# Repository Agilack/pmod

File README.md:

# PMOD modules

This repository contains multiple projects of PMOD modules. All of them are
used for communications.

## CAN

This module is a peripheral interface to connect a CAN bus.

## RS232

This module is a RS232 interface. The PMOD side is a type4a interface and
the other side is a DB9 male connector. The module contains a level shifter
(basically a MAX3232) to allow interfacing RS232 signal levels on a board
with TTL levels.

## RS485

## Midi (IN)

This module can be used to connect a MIDI device to a board with PMOD interface.
The MIDI port is an input, so only instruments that send datas can be connected
(tested with a keyboard)

## USB Serial

This module is an usb-serial adapter (PMOD peripheral). Based on a Silicon Labs
chip, no specific driver is required to use it on most OS.

## Wifi

This module is a Wifi interface (PMOD peripheral). Based on the very popular
espressif chip (ESP8285 or ESP8266)

# License

All electronics parts are released under Creative Commons Attribution Share
Alike 3.0 license.

All firmwares and softwares included with modules are realeased under GNU
General Public Licence v3 (GNU GPLv3)

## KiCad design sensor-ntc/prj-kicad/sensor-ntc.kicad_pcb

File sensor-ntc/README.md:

NTC Sensor
==========

This PMOD peripheral is a data acquisition module for temperature sensor (NTC).

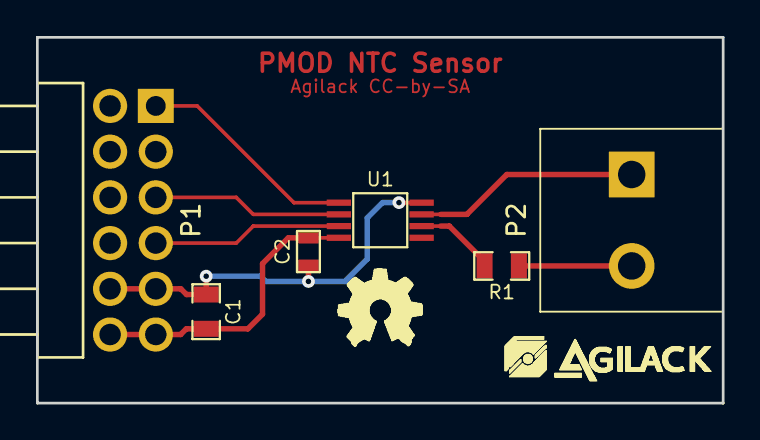
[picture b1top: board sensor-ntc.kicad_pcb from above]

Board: 2 copper layers, 38.1 x 20.3 mm, 8 parts (0 on the bottom side), 8 nets.

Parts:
C1: 1uF; SMD0805
C2: 100nF; SMD0603
P1: PMOD; CONN_PMOD-Male
P2: CONN_2; CONN_MC000034
R1: R; SMD0805
U1: MAX6682; MSOP8
agilack-11.5: 450px; logo-agilack-11.5
ohw_logo: VAL**; Logo-ohw

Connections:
GND: C1.2, C2.2, P1.5, P1.11, U1.4
unnamed: P2.1, U1.3
unnamed: P2.2, R1.2
unnamed: R1.1, U1.2
SPI_CS: P1.1, U1.5
SPI_MISO: P1.3, U1.6
SPI_SCK: P1.4, U1.7
VCC: C1.1, C2.1, P1.6, P1.12, U1.8

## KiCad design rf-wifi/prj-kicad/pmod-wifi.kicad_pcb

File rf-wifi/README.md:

PMOD Wifi
=========

This PMOD peripheral allow to quickly add a Wifi interface to a development
board. The embedded espressif chip (ESP8285 or ESP8266) can act as a station
(client) or as an access point (AP).

The PMOD connector use a type 4A interface (UART 12 pins).

Design
------

            Schematics            |              Routing
--------------------------------- | ---------------------------------
 |

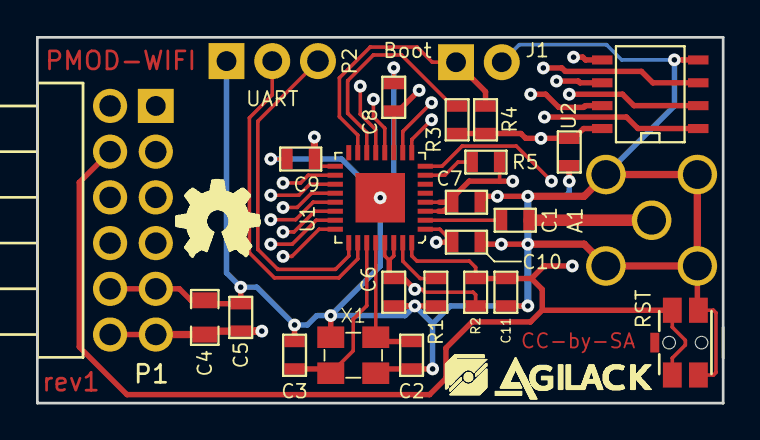
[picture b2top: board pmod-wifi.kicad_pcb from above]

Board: 4 copper layers, 38.1 x 20.3 mm, 27 parts (0 on the bottom side), 24 nets.

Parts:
A1: ANTENNA; CONN_SMA_RA
C1: 5.6pF; SMD0603
C2, C3: 10pF; SMD0603
C4: 10uF; SMD0805
C5, C6, C7, C8, C9, C10, C12: 100nF; SMD0603
C11: 1uF; SMD0603
J1: JUMPER; CONN_2
LOGO-OHW: VAL**; logo-ohw
P1: PMOD; CONN_PMOD-Male
P2: CONN_3
R1: 12k; SMD0603
R2, R3, R4, R5: 10k; SMD0603
SW1: SW_PUSH; SW_PTS840
U1: ESP8285; QFN32
U2: M25P16-VME; SOIC-8E
X1: 26MHz; Q_3.2x2.5
agilack-11.5: 450px; logo-agilack-11.5

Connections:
+3.3V: C4.1, C5.1, C6.1, C7.1, C8.1, C9.1, C10.1, C12.1, P1.6, P1.12, R2.1, R3.1, R4.1, R5.1, U1.1, U1.3, U1.4, U1.11, U1.17, U1.29, U1.30, U2.8
/CFG1: R3.2, U1.14
BOOT: J1.1, R4.2, U1.15
GND: A1.2, C2.2, C3.2, C4.2, C5.2, C6.2, C7.2, C8.2, C9.2, C10.2, C11.2, C12.2, J1.2, P1.5, P1.11, P2.1, R1.2, SW1.2, U1.PAD, U2.4, X1.2, X1.4
MEM_CLK: U1.21, U2.6
MEM_CS: U1.20, U2.1
MEM_HOLD: U1.18, U2.7
MEM_MISO: U1.22, U2.2
MEM_MOSI: U1.23, U2.5
MEM_WP: U1.19, U2.3
unnamed: A1.1, C1.1
unnamed: C1.2, U1.2
unnamed: C2.1, U1.28, X1.3
unnamed: C3.1, U1.27, X1.1
unnamed: R1.1, U1.31
unnamed: R5.2, U1.7
RST: C11.1, P1.8, R2.2, SW1.1, U1.8, U1.32
SPI_CS: P1.1, U1.13
SPI_INT: P1.7, U1.24
SPI_MISO: P1.3, U1.10
SPI_MOSI: P1.2, U1.12
SPI_SCK: P1.4, U1.9
UART_RX: P2.3, U1.25
UART_TX: P2.2, U1.26

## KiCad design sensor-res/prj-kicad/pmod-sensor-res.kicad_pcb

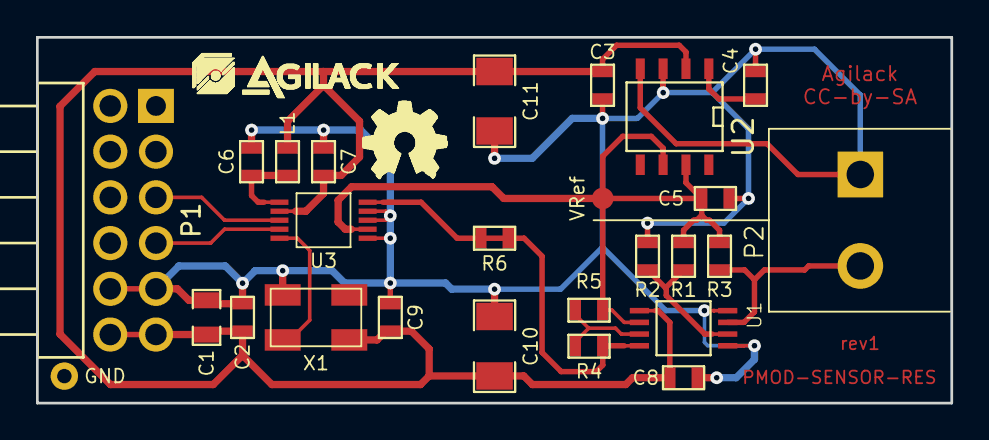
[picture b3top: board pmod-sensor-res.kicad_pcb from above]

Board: 2 copper layers, 50.8 x 20.3 mm, 28 parts (0 on the bottom side), 12 nets.

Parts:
C1: 10uF; SMD0805
C2, C3, C4, C6, C7, C8, C9: 100nF; SMD0603
C5: 1uF; SMD0603
C10, C11: 2,2uF; SMD1206
L1: FB100; SMD0603
LOGO-OHW: VAL**; logo-ohw
P1: PMOD; CONN_PMOD-Male
P2: CONN_2; MC000034
R1, R3: 10k; SMD0603
R2: 100; SMD0603
R4, R5: R; SMD0603
R6: 0; SMD0603
TP1: CONN_1; TP_SMD
TP2: CONN_1; TP
U1: AD8237; TSSOP8
U2: MAX6126; SOIC-8E
U3: MAX11201; MSOP-10
X1: OSC; Q_SMD5x3
agilack-11.5: 450px; logo-agilack-11.5

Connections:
+3.3V: C1.1, C2.1, C3.1, C7.1, C8.1, C9.1, C10.1, C11.1, L1.1, P1.6, P1.12, U1.5, U2.2, U3.7, X1.4
+VSensor: C5.1, R1.2, R3.1, R5.1, TP1.1, U1.6, U2.6, U2.7, U3.2
/S_IN: P2.2, R3.2, U1.3
/S_REF: R1.1, R2.2, U1.2
GND: C1.2, C2.2, C3.2, C4.2, C5.2, C6.2, C7.2, C8.2, C9.2, C10.2, C11.2, P1.5, P1.11, P2.1, R2.1, TP2.1, U1.1, U1.4, U2.3, U2.4, U3.1, U3.3, U3.4, X1.2
MCLK: U3.10, X1.3
unnamed: C4.1, U2.1
unnamed: C6.1, L1.2, U3.6
unnamed: R4.1, R5.2, U1.7
unnamed: R4.2, R6.1, R6.2, U1.8, U3.5
SPI_MISO: P1.3, U3.8
SPI_SCK: P1.4, U3.9

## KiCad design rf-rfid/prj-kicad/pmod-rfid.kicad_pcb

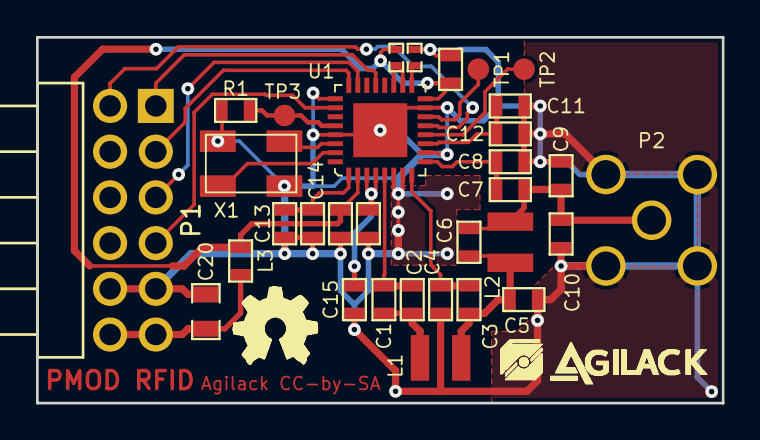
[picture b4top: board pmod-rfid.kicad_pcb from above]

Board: 2 copper layers, 38.1 x 20.3 mm, 34 parts (0 on the bottom side), 24 nets.

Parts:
C1, C2: 1,5nF; SMD0603
C3, C4: 1,2nF; SMD0603
C5, C8: 680pF; SMD0603
C6: 10pF; SMD0603
C7: 220pF; SMD0603
C9: 100pF; SMD0603
C10: 27pF; SMD0603
C11, C13, C15: 2,2uF; SMD0603
C12, C14, C16: 10nF; SMD0603
C18, C19: 100nF; SMD0603
C20: C; SMD0805
L1: INDUCTOR; I_1008CS
L2: 330nH; I_1008CS
L3: FB1000; SMD0603
P1: PMOD; CONN_PMOD-Male
P2: ANTENNA; CONN_SMA_RA
R1: 10k; SMD0603
R2, R3: 0; SMD0402
TP1, TP2, TP3: CONN_1; TP_SMD
U1: TRF7970; QFN32
X1: 13,56MHz; Q_SMD5x3
agilack-11.5: 450px; logo-agilack-11.5
ohw_logo: VAL**; logo-ohw

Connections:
+3.3V: C20.1, L3.1, P1.6, P1.12
+Vrfid: C18.1, C19.1, L3.2, R3.1, U1.2, U1.16
GND: C4.2, C5.2, C8.2, C9.2, C10.2, C11.2, C12.2, C13.2, C14.2, C15.2, C16.2, C18.2, C19.2, C20.2, P1.5, P1.11, P2.2, R1.1, R2.2, U1.6, U1.7, U1.10, U1.15, U1.25, U1.29, U1.PAD, X1.2, X1.4
unnamed: C1.1, C2.1, L1.1
unnamed: C1.2, C2.2, U1.5
unnamed: C3.1, C5.1, C6.2, L1.2, L2.1
unnamed: C3.2, C4.1, U1.8
unnamed: C7.2, C8.1, U1.9
unnamed: C6.1, C7.1, C9.1, C10.1, L2.2, P2.1
unnamed: C11.1, C12.1, U1.11
unnamed: C13.1, C14.1, U1.1
unnamed: C15.1, C16.1, U1.3, U1.4
unnamed: R1.2, TP3.1, U1.28
unnamed: TP1.1, U1.14
unnamed: TP2.1, U1.12
unnamed: U1.30, X1.3
unnamed: U1.31, X1.1
SPI_CFG0: R2.1, U1.17
SPI_CFG1: R3.2, U1.18, U1.19
SPI_IT: P1.7, U1.13
SPI_MISO: P1.3, U1.23
SPI_MOSI: P1.2, U1.24
SPI_NSS: P1.1, U1.21
SPI_SCK: P1.4, U1.26

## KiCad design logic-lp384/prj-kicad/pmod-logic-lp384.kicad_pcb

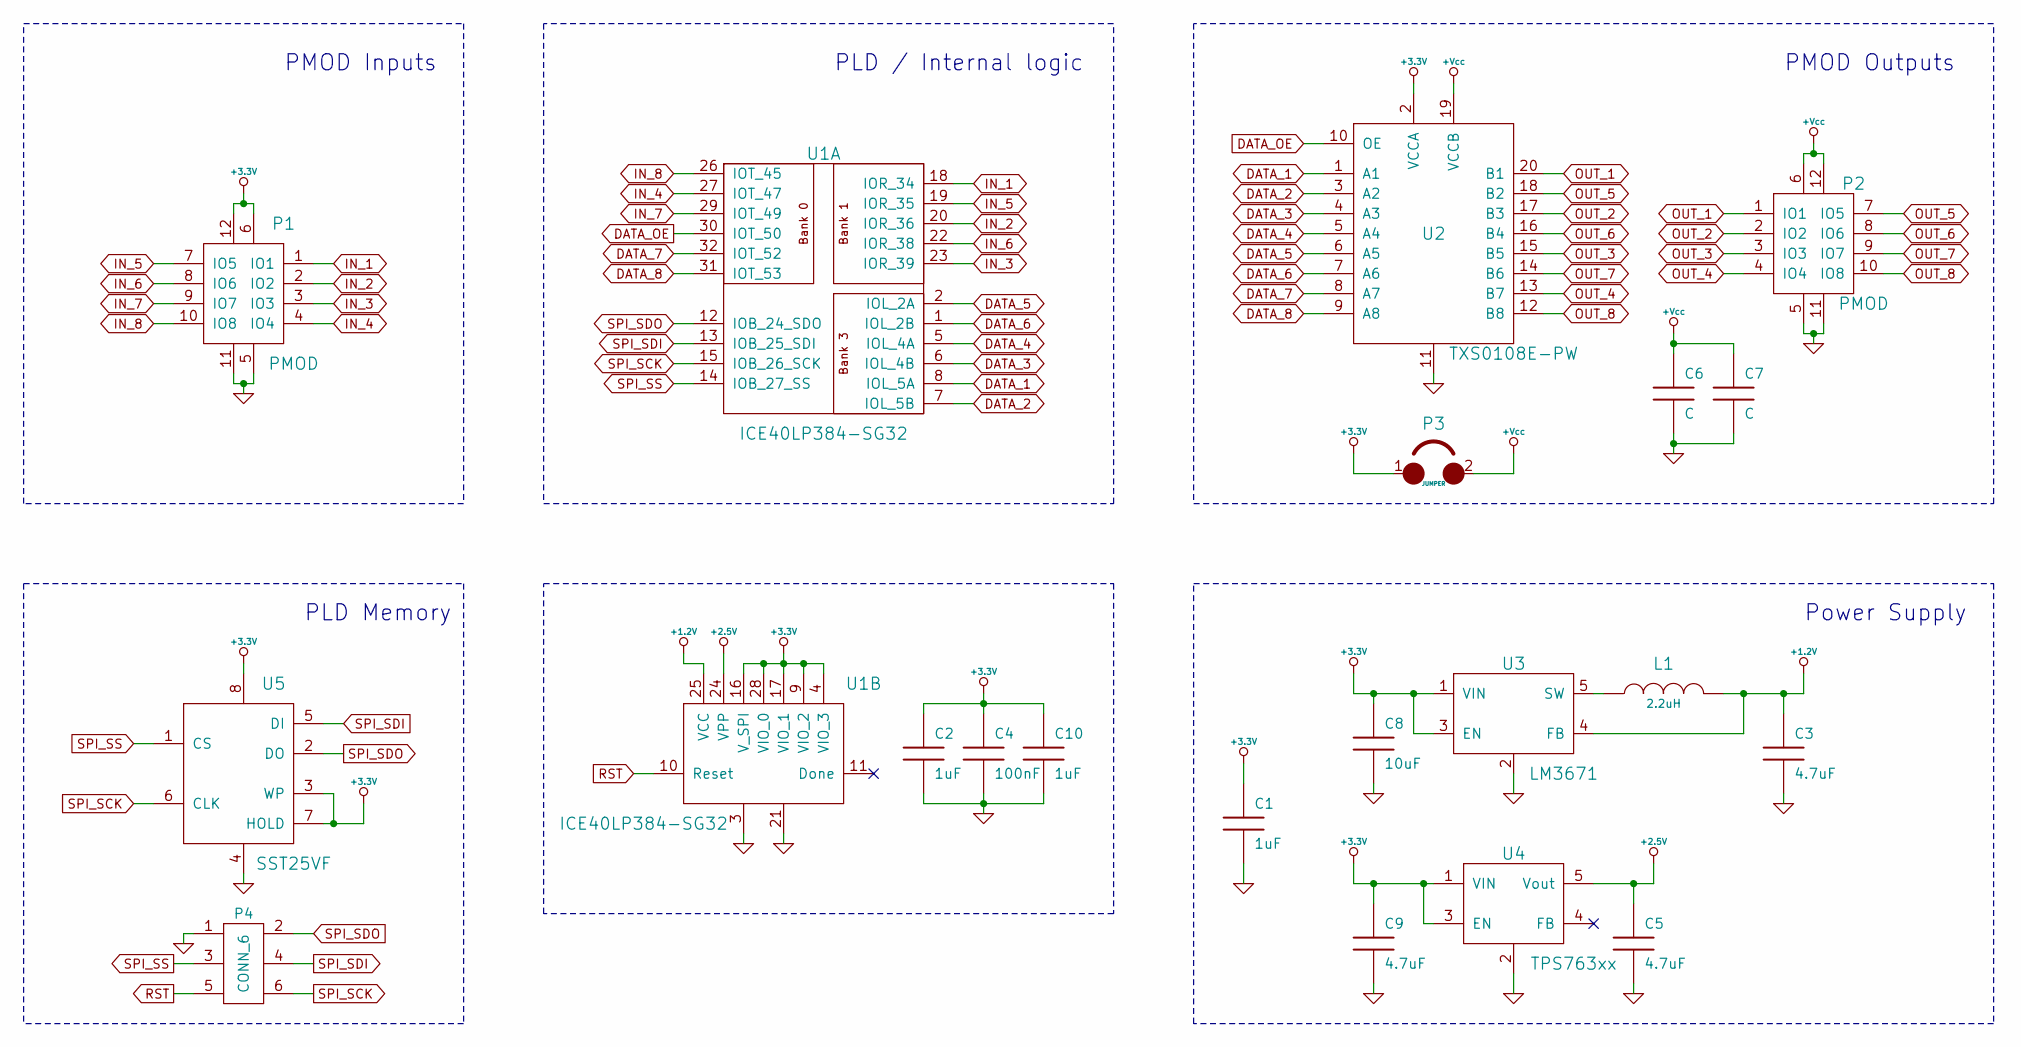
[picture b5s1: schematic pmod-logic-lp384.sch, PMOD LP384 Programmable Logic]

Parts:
C1: 1uF; SMD0805
C2, C10: 1uF; SMD0603
C3, C5, C9: 4.7uF; SMD0603
C4: 100nF; SMD0603
C6, C7: C; SMD0603
C8: 10uF; SMD0805
L1: 2.2uH; SMD0603
P1: PMOD; CONN_PMOD-Male
P2: PMOD; PMOD_SSW106-RA
P3: JUMPER; CONN_2
P4: CONN_6
U1: ICE40LP384-SG32; QFN32
U2: TXS0108E-PW; TSSOP20
U3: LM3671; SOT23-5
U4: TPS763xx; SOT23-5
U5: SST25VF; SMD_SO8E

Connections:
+1.2V: C3.1, L1.2, U1.25 (VCC), U3.4 (FB)
+2.5V: C5.1, U1.24 (VPP), U4.5 (Vout)
+3.3V: C1.1, C2.1, C4.1, C8.1, C9.1, C10.1, P1.6, P1.12, P3.1, U1.4 (VIO_3), U1.9 (VIO_2), U1.16 (V_SPI), U1.17 (VIO_1), U1.28 (VIO_0), U2.2 (VCCA), U3.1 (VIN), U3.3 (EN), U4.1 (VIN), U4.3 (EN), U5.3 (WP), U5.7 (HOLD), U5.8
+Vcc: C6.1, C7.1, P2.6, P2.12, P3.2, U2.19 (VCCB)
DATA_1: U1.8 (IOL_5A), U2.1 (A1)
DATA_2: U1.7 (IOL_5B), U2.3 (A2)
DATA_3: U1.6 (IOL_4B), U2.4 (A3)
DATA_4: U1.5 (IOL_4A), U2.5 (A4)
DATA_5: U1.2 (IOL_2A), U2.6 (A5)
DATA_6: U1.1 (IOL_2B), U2.7 (A6)
DATA_7: U1.32 (IOT_52), U2.8 (A7)
DATA_8: U1.31 (IOT_53), U2.9 (A8)
DATA_OE: U1.30 (IOT_50), U2.10 (OE)
GND: C1.2, C2.2, C3.2, C4.2, C5.2, C6.2, C7.2, C8.2, C9.2, C10.2, P1.5, P1.11, P2.5, P2.11, P4.1, U1.3, U1.21, U2.11, U3.2, U4.2, U5.4
IN_1: P1.1 (IO1), U1.18 (IOR_34)
IN_2: P1.2 (IO2), U1.20 (IOR_36)
IN_3: P1.3 (IO3), U1.23 (IOR_39)
IN_4: P1.4 (IO4), U1.27 (IOT_47)
IN_5: P1.7 (IO5), U1.19 (IOR_35)
IN_6: P1.8 (IO6), U1.22 (IOR_38)
IN_7: P1.9 (IO7), U1.29 (IOT_49)
IN_8: P1.10 (IO8), U1.26 (IOT_45)
unnamed: L1.1, U3.5 (SW)
OUT_1: P2.1 (IO1), U2.20 (B1)
OUT_2: P2.2 (IO2), U2.17 (B3)
OUT_3: P2.3 (IO3), U2.15 (B5)
OUT_4: P2.4 (IO4), U2.13 (B7)
OUT_5: P2.7 (IO5), U2.18 (B2)
OUT_6: P2.8 (IO6), U2.16 (B4)
OUT_7: P2.9 (IO7), U2.14 (B6)
OUT_8: P2.10 (IO8), U2.12 (B8)
RST: P4.5, U1.10 (Reset)
SPI_SCK: P4.6, U1.15 (IOB_26_SCK), U5.6 (CLK)
SPI_SDI: P4.4, U1.13 (IOB_25_SDI), U5.5 (DI)
SPI_SDO: P4.2, U1.12 (IOB_24_SDO), U5.2 (DO)
SPI_SS: P4.3, U1.14 (IOB_27_SS), U5.1 (CS)

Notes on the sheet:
PLD Memory
Power Supply
PMOD Inputs
PMOD Outputs
PLD / Internal logic

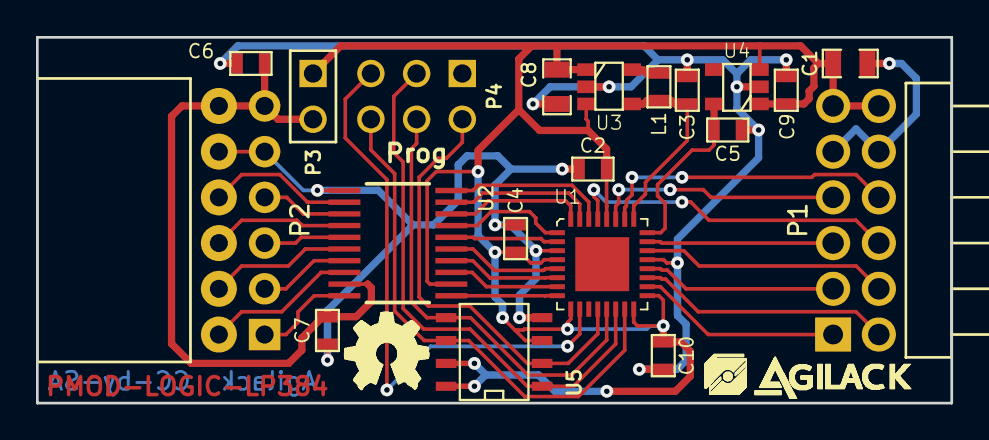
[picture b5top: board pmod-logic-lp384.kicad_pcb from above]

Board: 2 copper layers, 50.8 x 20.3 mm, 22 parts (0 on the bottom side), 36 nets.

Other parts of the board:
agilack-11.5: 450px; agilack-11.5
ohw_logo: VAL**; ohw-logo

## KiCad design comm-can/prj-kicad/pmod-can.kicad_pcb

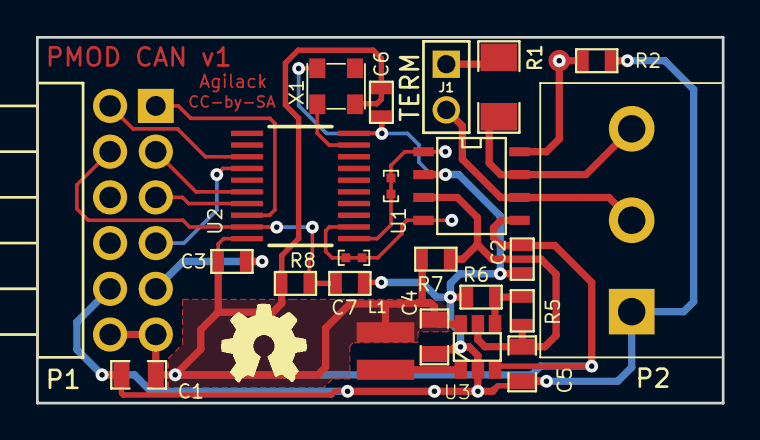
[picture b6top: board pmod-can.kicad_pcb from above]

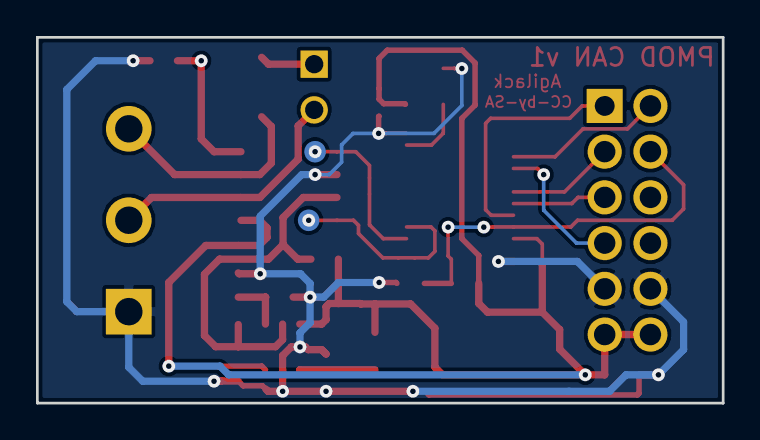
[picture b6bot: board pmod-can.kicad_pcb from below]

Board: 2 copper layers, 38.1 x 20.3 mm, 27 parts (2 on the bottom side), 18 nets.

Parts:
C1, C4, C5: 10uF; SMD0805
C2, C3, C6: 100nF; SMD0603
C7: C; SMD0603
J1: JUMPER; CONN_2
L1: 4,7uH; I_EPL3010
P1: PMOD; CONN_PMOD-Male
P2: CONN_3; CONN_MC000035
R1: R; SMD1206
R2, R5, R6, R8: R; SMD0603
R3, R4: 0; SMD0402
R7: 0; SMD0603
TP2, TP3, TP4: CONN_1; TP_SMD
U1: MCP2562; SOIC-8E
U2: MCP2515-ST; TSSOP20
U3: TLV61220; SOT23-6
X1: 8MHz; Q_DFN3225
logo_ohw: VAL**; logo-ohw

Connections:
5V: C5.1, R5.1, R7.2, U1.3, U3.5
/CAN_H: J1.2, P2.2, U1.6
/CAN_L: P2.3, R1.1, U1.7
CAN_RX: R4.1, R4.2, TP3.1, U1.4, U2.2
CAN_TX: R3.1, R3.2, TP2.1, U1.1, U2.1
GND: C1.2, C2.2, C3.2, C4.2, C5.2, C6.2, C7.2, P1.5, P1.11, P2.1, R2.2, R6.2, U1.2, U2.10, U3.2, X1.2
unnamed: J1.1, R1.2
unnamed: L1.2, U3.1
unnamed: R2.1, TP4.1, U1.8
unnamed: R5.2, R6.1, U3.4
unnamed: U2.9, X1.3
RST: C7.1, P1.8, R8.2, U2.19
SPI_CS: P1.1, U2.18
SPI_INT: P1.7, U2.13
SPI_MISO: P1.3, U2.17
SPI_MOSI: P1.2, U2.16
SPI_SCK: P1.4, U2.14
VCC: C1.1, C2.1, C3.1, C4.1, C6.1, L1.1, P1.6, P1.12, R7.1, R8.1, U1.5, U2.20, U3.3, U3.6, X1.4

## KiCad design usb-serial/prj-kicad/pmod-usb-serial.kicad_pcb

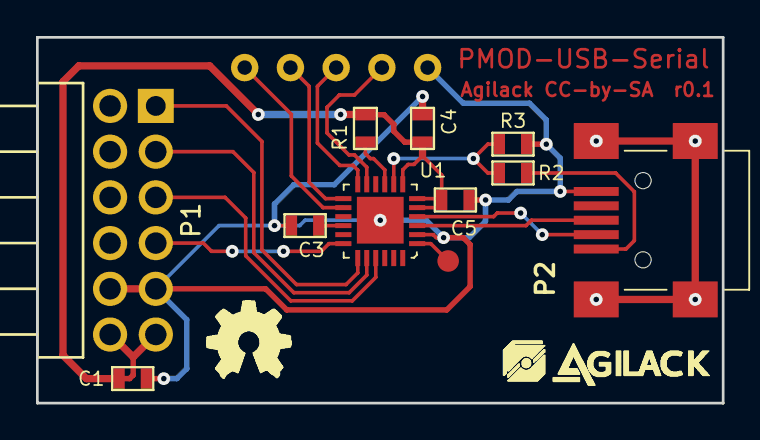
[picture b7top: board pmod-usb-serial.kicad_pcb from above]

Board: 2 copper layers, 38.1 x 20.3 mm, 18 parts (0 on the bottom side), 17 nets.

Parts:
C1, C4: 1uF; SMD0603
C3: 4,7uF; SMD0603
C5: 100nF; SMD0603
P1: PMOD; CONN_PMOD-Male
P2: CONN_MiniUSB-AB; CONN_65100516121
R1: 4,7k; SMD0603
R2, R3: R; SMD0603
TP1, TP2, TP3, TP4, TP5: CONN_1; TP_PIN
TP6: CONN_1; TP_SMD
U1: CP2104; QFN24
agilack-11.5: 450px; logo-agilack-11.5
logo_ohw: VAL**; logo-ohw

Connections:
GND: C1.2, C3.2, C4.2, C5.2, P1.5, P1.11, P2.5, R3.1, TP5.1, U1.2, U1.PAD
unnamed: C3.1, U1.16
unnamed: P2.1, R2.2
unnamed: P2.2, U1.4
unnamed: P2.3, U1.3
unnamed: R2.1, R3.2, U1.8
unnamed: TP1.1, U1.14
unnamed: TP2.1, U1.13
unnamed: TP3.1, U1.12
unnamed: TP4.1, U1.11
unnamed: TP6.1, U1.1
PMOD_CTS: P1.1, U1.19
PMOD_RTS: P1.4, U1.18
PMOD_RXD: P1.3, U1.21
PMOD_TXD: P1.2, U1.20
RST: R1.2, U1.9
VCC: C1.1, C4.1, C5.1, P1.6, P1.12, R1.1, U1.5, U1.6, U1.7

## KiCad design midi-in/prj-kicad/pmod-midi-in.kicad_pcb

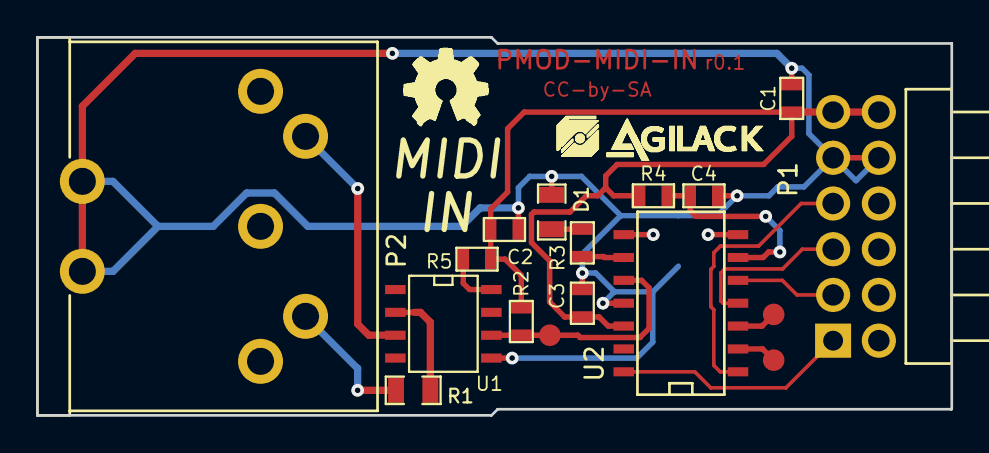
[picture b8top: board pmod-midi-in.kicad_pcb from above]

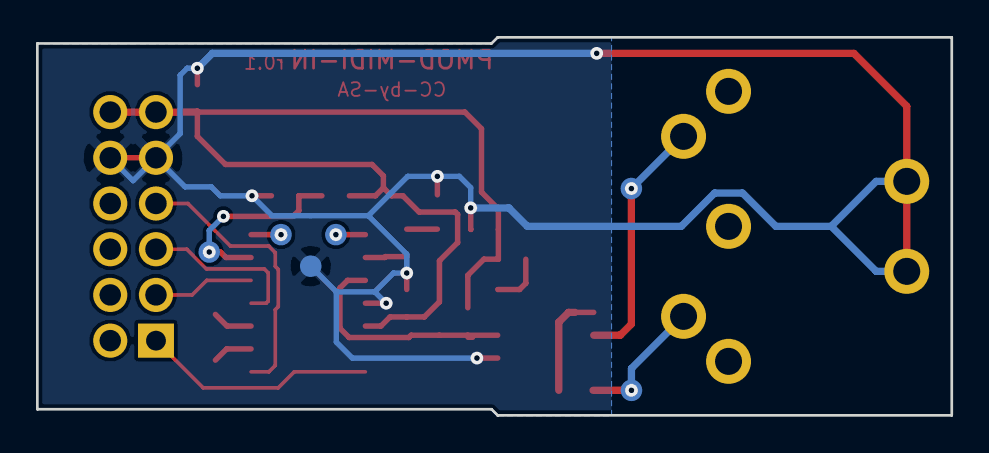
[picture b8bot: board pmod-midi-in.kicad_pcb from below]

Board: 2 copper layers, 50.8 x 21.0 mm, 25 parts (6 on the bottom side), 18 nets.

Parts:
C1, C4: 1uF; SMD0603
C2, C3: 100nF; SMD0603
D1: LED; SMD0805
P1: PMOD; CONN_PMOD-Male
P2: DIN5; CONN-DIN_0105_05
R1: 220; SMD0805
R2, R4: 10k; SMD0603
R3: 330; SMD0603
R5: 100; SMD0603
TP1, TP2, TP3, TP4, TP5, TP6, TP7, TP8, TP9: CONN_1; TP_SMD
U1: SFH6318; SOIC-8E
U2: ATSAMD09C13A; SOIC-14
agilack-11.5: 450px; logo-agilack-11.5
logo_ohw: VAL**; logo-ohw

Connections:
/SWDCLK: TP1.1, U2.7
/SWDIO: TP2.1, U2.8
GND: C1.2, C2.2, C3.2, C4.2, D1.2, P1.5, P1.11, P2.0, TP7.1, U1.5, U2.11
LED: R3.1, U2.9
MIDI_IN: R2.2, TP3.1, U1.6, U2.10
unnamed: D1.1, R3.2
unnamed: P2.4, R1.2, TP5.1
unnamed: P2.5, TP6.1, U1.3
unnamed: R1.1, U1.2
unnamed: R5.2, U1.8
unnamed: TP8.1, U2.2
unnamed: TP9.1, U2.3
PMOD_CTS: P1.1, U2.14
PMOD_RTS: P1.4, U2.1
PMOD_RXD: P1.3, U2.4
PMOD_TXD: P1.2, U2.5
RST: C4.1, R4.2, TP4.1, U2.6
VCC: C1.1, C2.1, C3.1, P1.6, P1.12, R2.1, R4.1, R5.1, U2.12

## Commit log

2017-06-28 Create new module : RS232 transceiver (with DB9 connector)
2017-06-30 RS232: Generate production files (gerber and drill)
2017-07-10 RS485: Create a new module for RS485 interface - Add schematics
2017-07-11 RS485: Add board netlist and routing
2017-07-13 RS485: Generate production files (gerber and drill)
2017-07-18 RS232: Insert picture of the first prototype with components
2017-07-20 RS485: Insert picture of the first prototype with components
2017-07-21 Update main readme file
2017-08-28 MIDI-IN: Create a new module for aMIDI interface (input only)
2017-08-30 MIDI-IN: add board design (netlist and routing)
2017-08-30 MIDI-IN: Generate production files (gerbers and drill)
2017-08-31 MIDI-IN: Create a skeleton for embedded firmware
2017-08-31 MIDI-IN: Improve firmware, add a basic loop to read/send midi datas
2017-09-01 MIDI-IN: Add a unit-test to read and decode MIDI datas ("quick and dirty" code)
2017-09-06 USB-serial: Create a new module with an USB-serial adapter
2017-09-08 USB-Serial: Create board (netlist and routing)
2017-09-12 USB-serial: Generate production files
2017-09-19 Small update of readme file, include new modules and license information
2017-09-22 MIDI-IN: Insert pictures of first prototype
2017-09-22 MIDI-IN: Fix picture path
2017-09-25 USB-serial: Insert picture of first prototype
2017-09-26 Comm-CAN: Create a new peripheral module to interface a CAN bus (schematics)
2017-09-27 Comm-CAN: Create footprint library for project
2017-09-27 Comm-CAN: Generate netlist
2017-09-28 Comm-CAN: Update board routing
2017-09-29 Comm-CAN: Generate production files
2017-10-02 Logic-LP384: Create a new PMOD :) Based on a small FPGA this module can be used as glue (or translator) between two other PMODs
2017-10-03 Logic-LP384: Update schematics
2017-10-05 Logic-LP384: Update routing
2017-10-08 Logic-LP384: Generate production files
2017-10-12 Comm-CAN: Insert picture of first prototype
2018-04-02 RF-RFID: Create a new PMOD :) This module is an RFID interface that can act as reader, writer or tag emulation
2018-04-03 RF-RFID: Create board skeleton
2018-04-03 RF-RFID: Add footprints library and create netlist
2018-04-04 RF-RFID: Update board routing
2018-04-04 RF-RFID: Update board silkscreen
2018-04-05 RF-RFID: Generate production files
2019-01-09 SENSOR-RES: Start board design / Full schematics
2019-01-10 SENSOR-RES: Create footprint library and board skeleton
2019-01-11 SENSOR-RES: Routing is now complete
2019-01-14 SENSOR-RES: Generate production files
2019-01-21 SENSOR-RES: Add pictures of the PCB (with components)
2019-02-18 RF-WIFI: --=={ New }==-- Start board design, create ESP8285 library (sch)
2019-02-19 RF-WIFI: Improve schematics, add all passive components and connectors
2019-02-20 RF-WIFI: Add components footprints and board routing
2019-02-21 RF-WIFI: Add external SPI flash (sch+pcb) for ESP8266 compatibility
2019-02-22 RF-WIFI: Generate production files
2019-02-27 RF-WIFI: Add a basic test software for embedded ESP
2019-03-04 RF-WIFI: Add pictures of the module (pcb+components)
2019-03-09 RF-WIFI: Add readme file and svg export of schematic and routing
2019-03-11 SENSOR-NTC: Create new PMOD to read NTC sensors temperature using dedicated chip
2019-03-12 SENSOR-NTC: Add board routing (footprint library, netlist and routing)
2019-03-15 SENSOR-NTC: Generate production files
2019-03-25 SENSOR-NTC: Add board picture

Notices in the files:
comm-can/prj-kicad/pmod-can.kicad_pcb:
CC-by-SA
rf-rfid/prj-kicad/pmod-rfid.kicad_pcb:
Agilack CC-by-SA
